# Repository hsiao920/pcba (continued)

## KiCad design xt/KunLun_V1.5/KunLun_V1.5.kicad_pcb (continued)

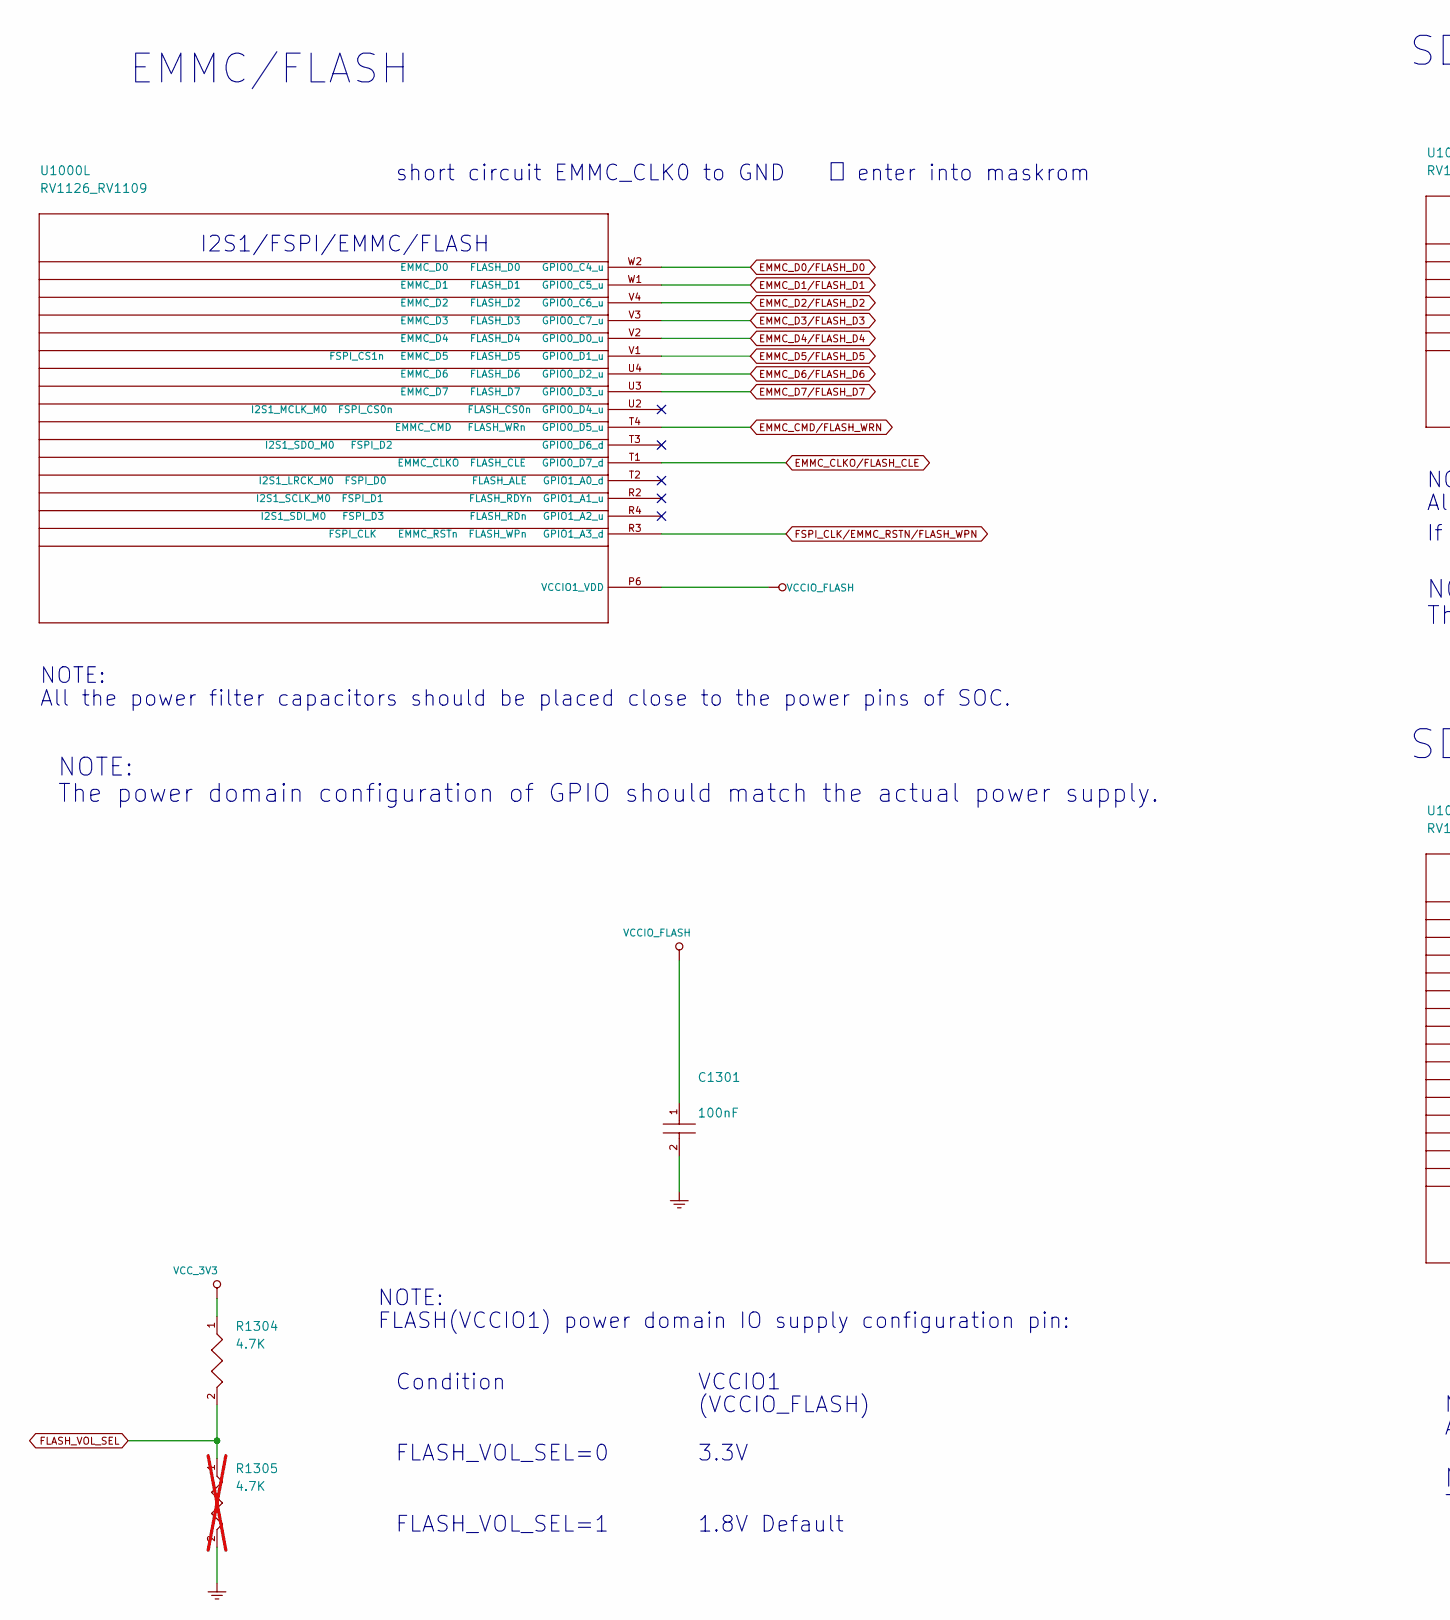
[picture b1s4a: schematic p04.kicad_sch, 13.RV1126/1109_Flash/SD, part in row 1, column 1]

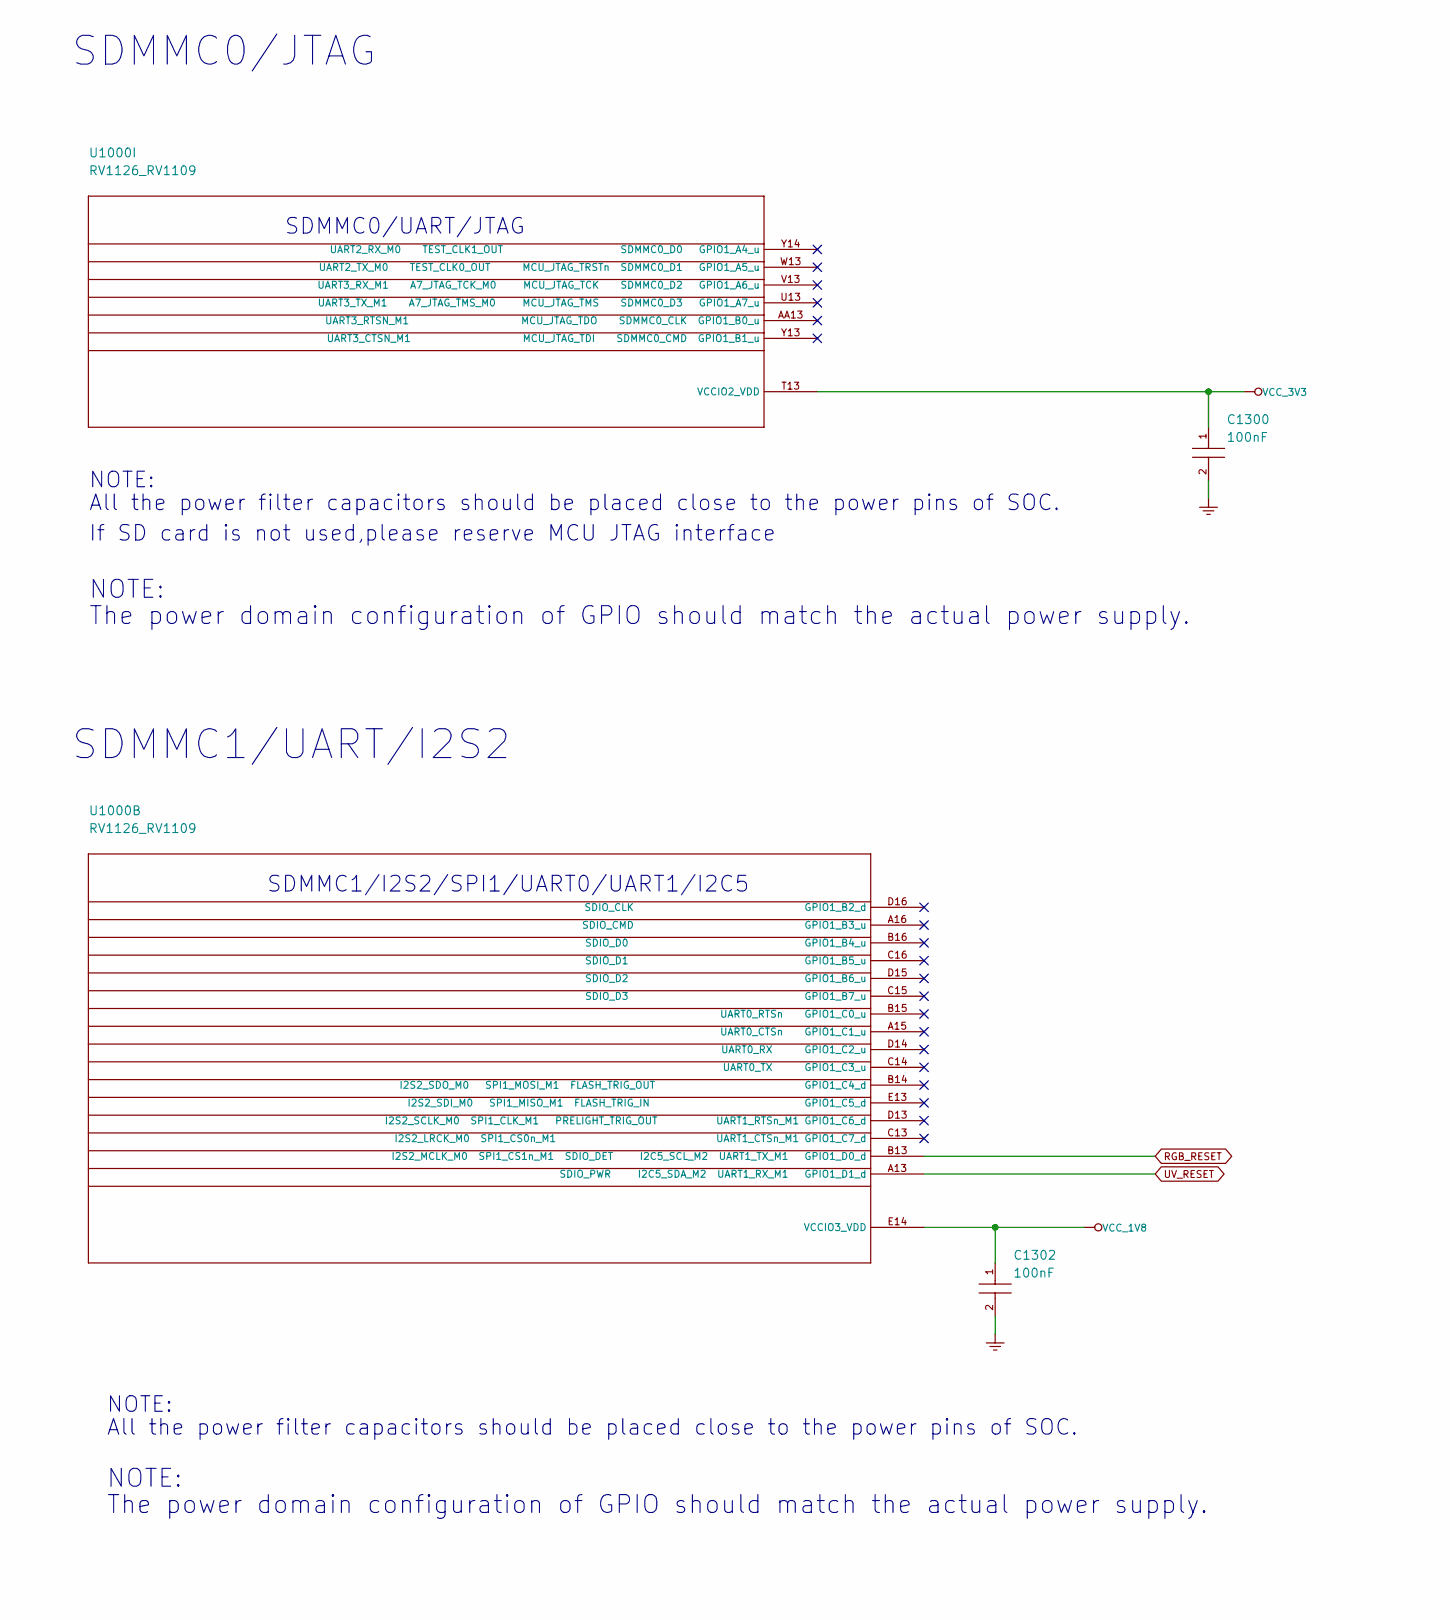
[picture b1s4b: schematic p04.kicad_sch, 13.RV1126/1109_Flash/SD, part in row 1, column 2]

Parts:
C1300, C1301, C1302: 100nF; C0201
R1304: 4.7K; R0402
R1305: 4.7K; R0402; not fitted
U1000: RV1126_RV1109; BGA409_14R00X14R00X0R90

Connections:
EMMC_CLKO/FLASH_CLE: U1000.T1 (EMMC_CLKO FLASH_CLE GPIO0_D7_d); also elsewhere on the board
EMMC_CMD/FLASH_WRN: U1000.T4 (EMMC_CMD FLASH_WRn GPIO0_D5_u); also elsewhere on the board
EMMC_D0/FLASH_D0: U1000.W2 (EMMC_D0 FLASH_D0 GPIO0_C4_u); also elsewhere on the board
EMMC_D1/FLASH_D1: U1000.W1 (EMMC_D1 FLASH_D1 GPIO0_C5_u); also elsewhere on the board
EMMC_D2/FLASH_D2: U1000.V4 (EMMC_D2 FLASH_D2 GPIO0_C6_u); also elsewhere on the board
EMMC_D3/FLASH_D3: U1000.V3 (EMMC_D3 FLASH_D3 GPIO0_C7_u); also elsewhere on the board
EMMC_D4/FLASH_D4: U1000.V2 (EMMC_D4 FLASH_D4 GPIO0_D0_u); also elsewhere on the board
EMMC_D5/FLASH_D5: U1000.V1 (FSPI_CS1n EMMC_D5 FLASH_D5 GPIO0_D1_u); also elsewhere on the board
EMMC_D6/FLASH_D6: U1000.U4 (EMMC_D6 FLASH_D6 GPIO0_D2_u); also elsewhere on the board
EMMC_D7/FLASH_D7: U1000.U3 (EMMC_D7 FLASH_D7 GPIO0_D3_u); also elsewhere on the board
FLASH_VOL_SEL: R1304.2, R1305.1; also elsewhere on the board
FSPI_CLK/EMMC_RSTN/FLASH_WPN: U1000.R3 (FSPI_CLK EMMC_RSTn FLASH_WPn GPIO1_A3_d); also elsewhere on the board
GND: C1300.2, C1301.2, C1302.2, R1305.2; also elsewhere on the board
RGB_RESET: U1000.B13 (I2S2_MCLK_M0 SPI1_CS1n_M1 SDIO_DET I2C5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); also elsewhere on the board
UV_RESET: U1000.A13 (SDIO_PWR I2C5_SDA_M2 UART1_RX_M1 GPIO1_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); also elsewhere on the board
VCCIO_FLASH: C1301.1, U1000.P6 (VCCIO1_VDD); also elsewhere on the board
VCC_1V8: C1302.1, U1000.E14 (VCCIO3_VDD); also elsewhere on the board
VCC_3V3: C1300.1, R1304.1, U1000.T13 (VCCIO2_VDD); also elsewhere on the board

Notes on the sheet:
EMMC/FLASH
SDMMC0/JTAG
SDMMC1/UART/I2S2
NOTE:
All the power filter capacitors should be placed close to the power pins of SOC.
FLASH(VCCIO1) power domain IO supply configuration pin:
3.3V
1.8V Default
FLASH_VOL_SEL=0
FLASH_VOL_SEL=1
VCCIO1
(VCCIO_FLASH)
Condition
If SD card is not used,please reserve MCU JTAG interface
The power domain configuration of GPIO should match the actual power supply.
short circuit EMMC_CLK0 to GND
enter into maskrom
SDMMC0/UART/JTAG
SDMMC1/I2S2/SPI1/UART0/UART1/I2C5
I2S1/FSPI/EMMC/FLASH

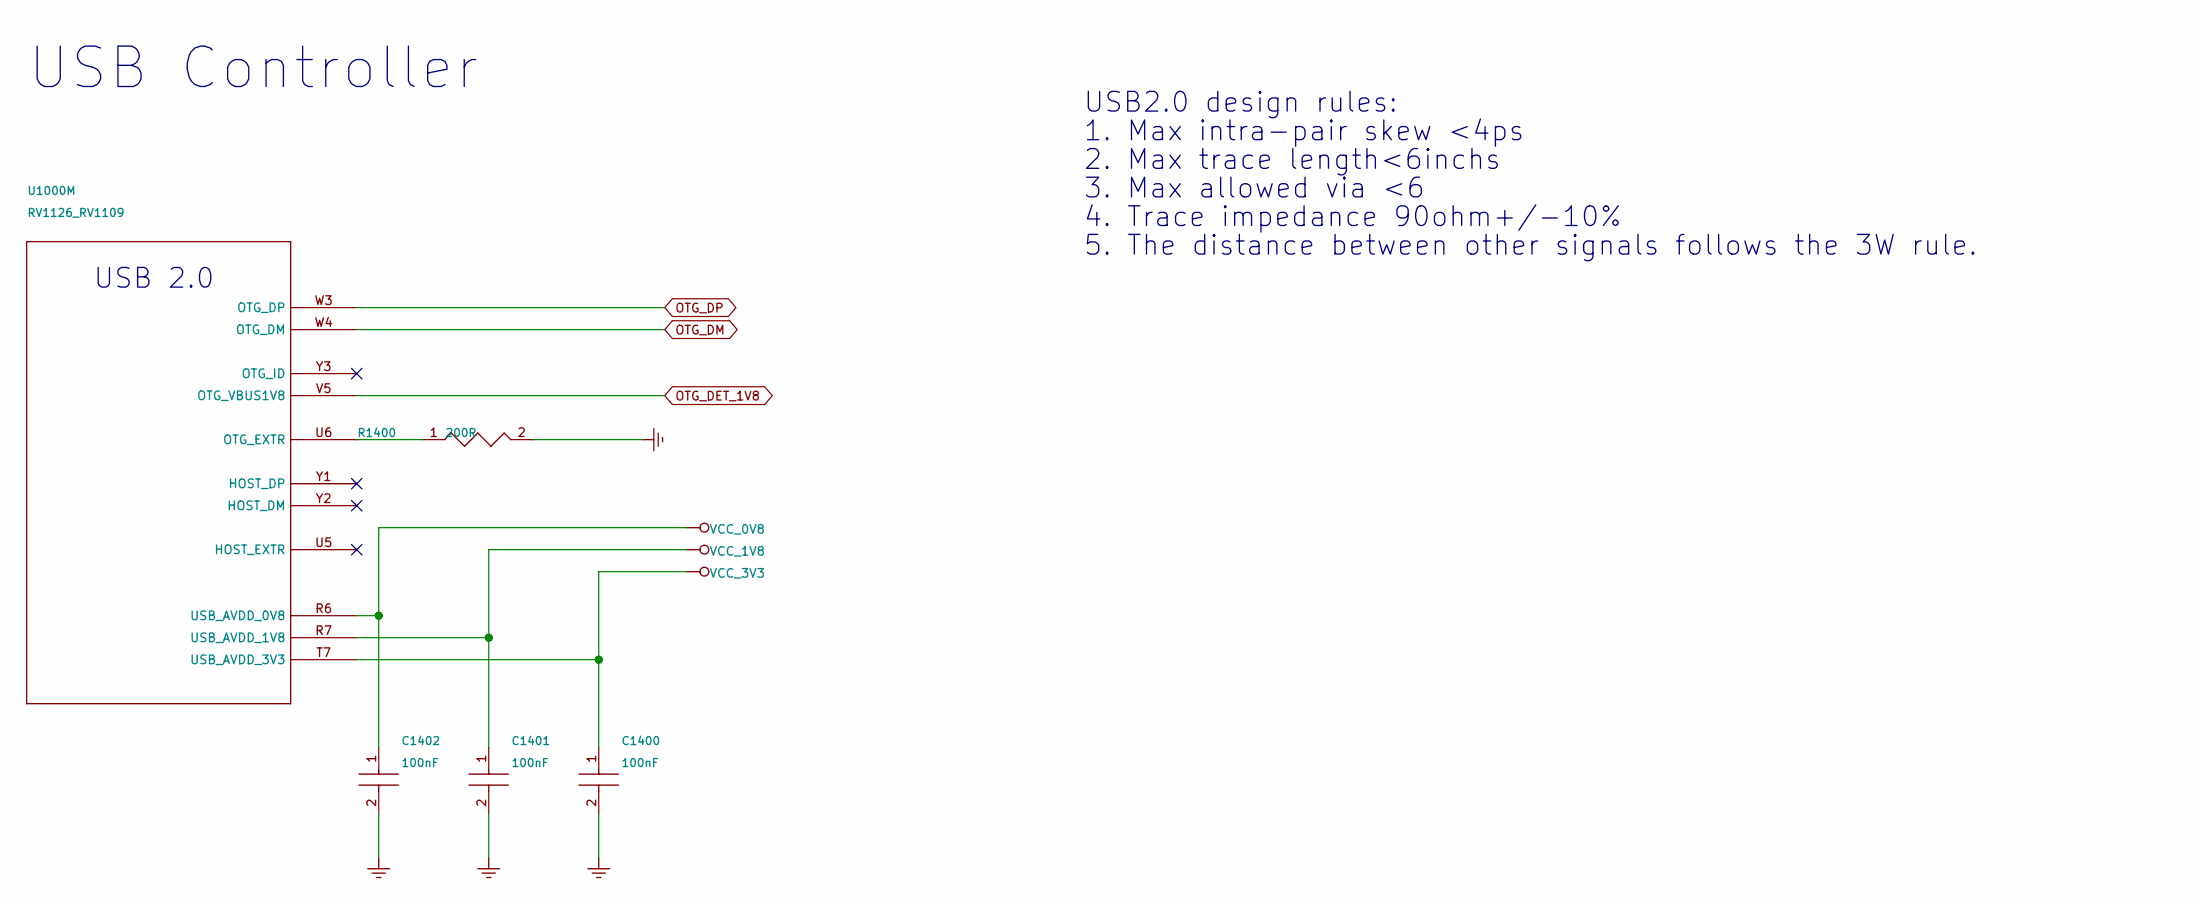
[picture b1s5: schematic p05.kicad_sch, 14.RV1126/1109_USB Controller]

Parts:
C1400, C1401, C1402: 100nF; C0201
R1400: 200R; R0402
U1000: RV1126_RV1109; BGA409_14R00X14R00X0R90

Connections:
GND: C1400.2, C1401.2, C1402.2, R1400.2; also elsewhere on the board
unnamed: R1400.1, U1000.U6 (OTG_EXTR)
OTG_DET_1V8: U1000.V5 (OTG_VBUS1V8); also elsewhere on the board
OTG_DM: U1000.W4 (OTG_DM); also elsewhere on the board
OTG_DP: U1000.W3 (OTG_DP); also elsewhere on the board
VCC_0V8: C1402.1, U1000.R6 (USB_AVDD_0V8); also elsewhere on the board
VCC_1V8: C1401.1, U1000.R7 (USB_AVDD_1V8); also elsewhere on the board
VCC_3V3: C1400.1, U1000.T7 (USB_AVDD_3V3); also elsewhere on the board

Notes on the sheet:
USB Controller
USB2.0 design rules:
1. Max intra-pair skew <4ps
2. Max trace length<6inchs
3. Max allowed via <6
4. Trace impedance 90ohm+/-10%
5. The distance between other signals follows the 3W rule.
USB 2.0

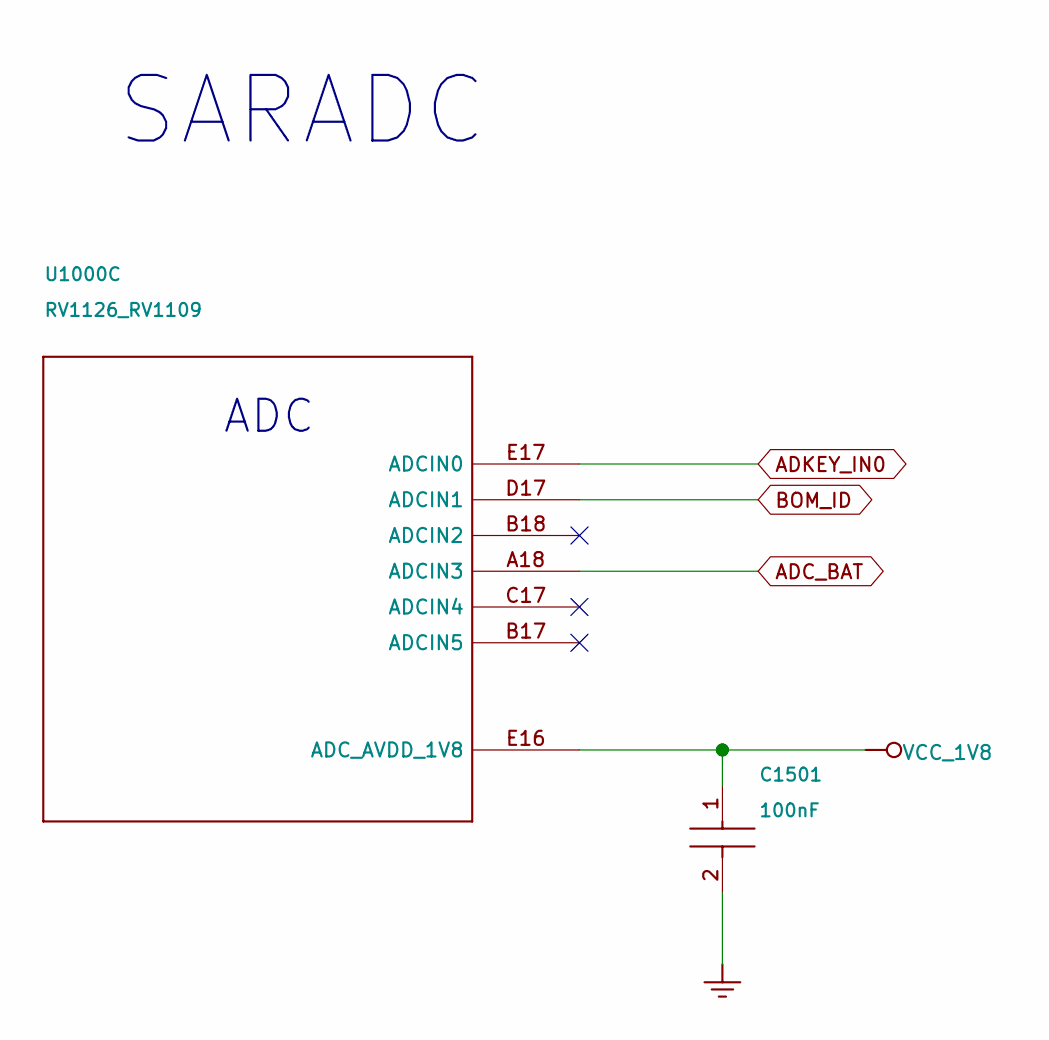
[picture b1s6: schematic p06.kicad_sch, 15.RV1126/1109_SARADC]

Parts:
C1501: 100nF; C0201
U1000: RV1126_RV1109; BGA409_14R00X14R00X0R90

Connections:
ADC_BAT: U1000.A18 (ADCIN3); also elsewhere on the board
ADKEY_IN0: U1000.E17 (ADCIN0)
BOM_ID: U1000.D17 (ADCIN1)
GND: C1501.2; also elsewhere on the board
VCC_1V8: C1501.1, U1000.E16 (ADC_AVDD_1V8); also elsewhere on the board

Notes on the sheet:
SARADC
ADC

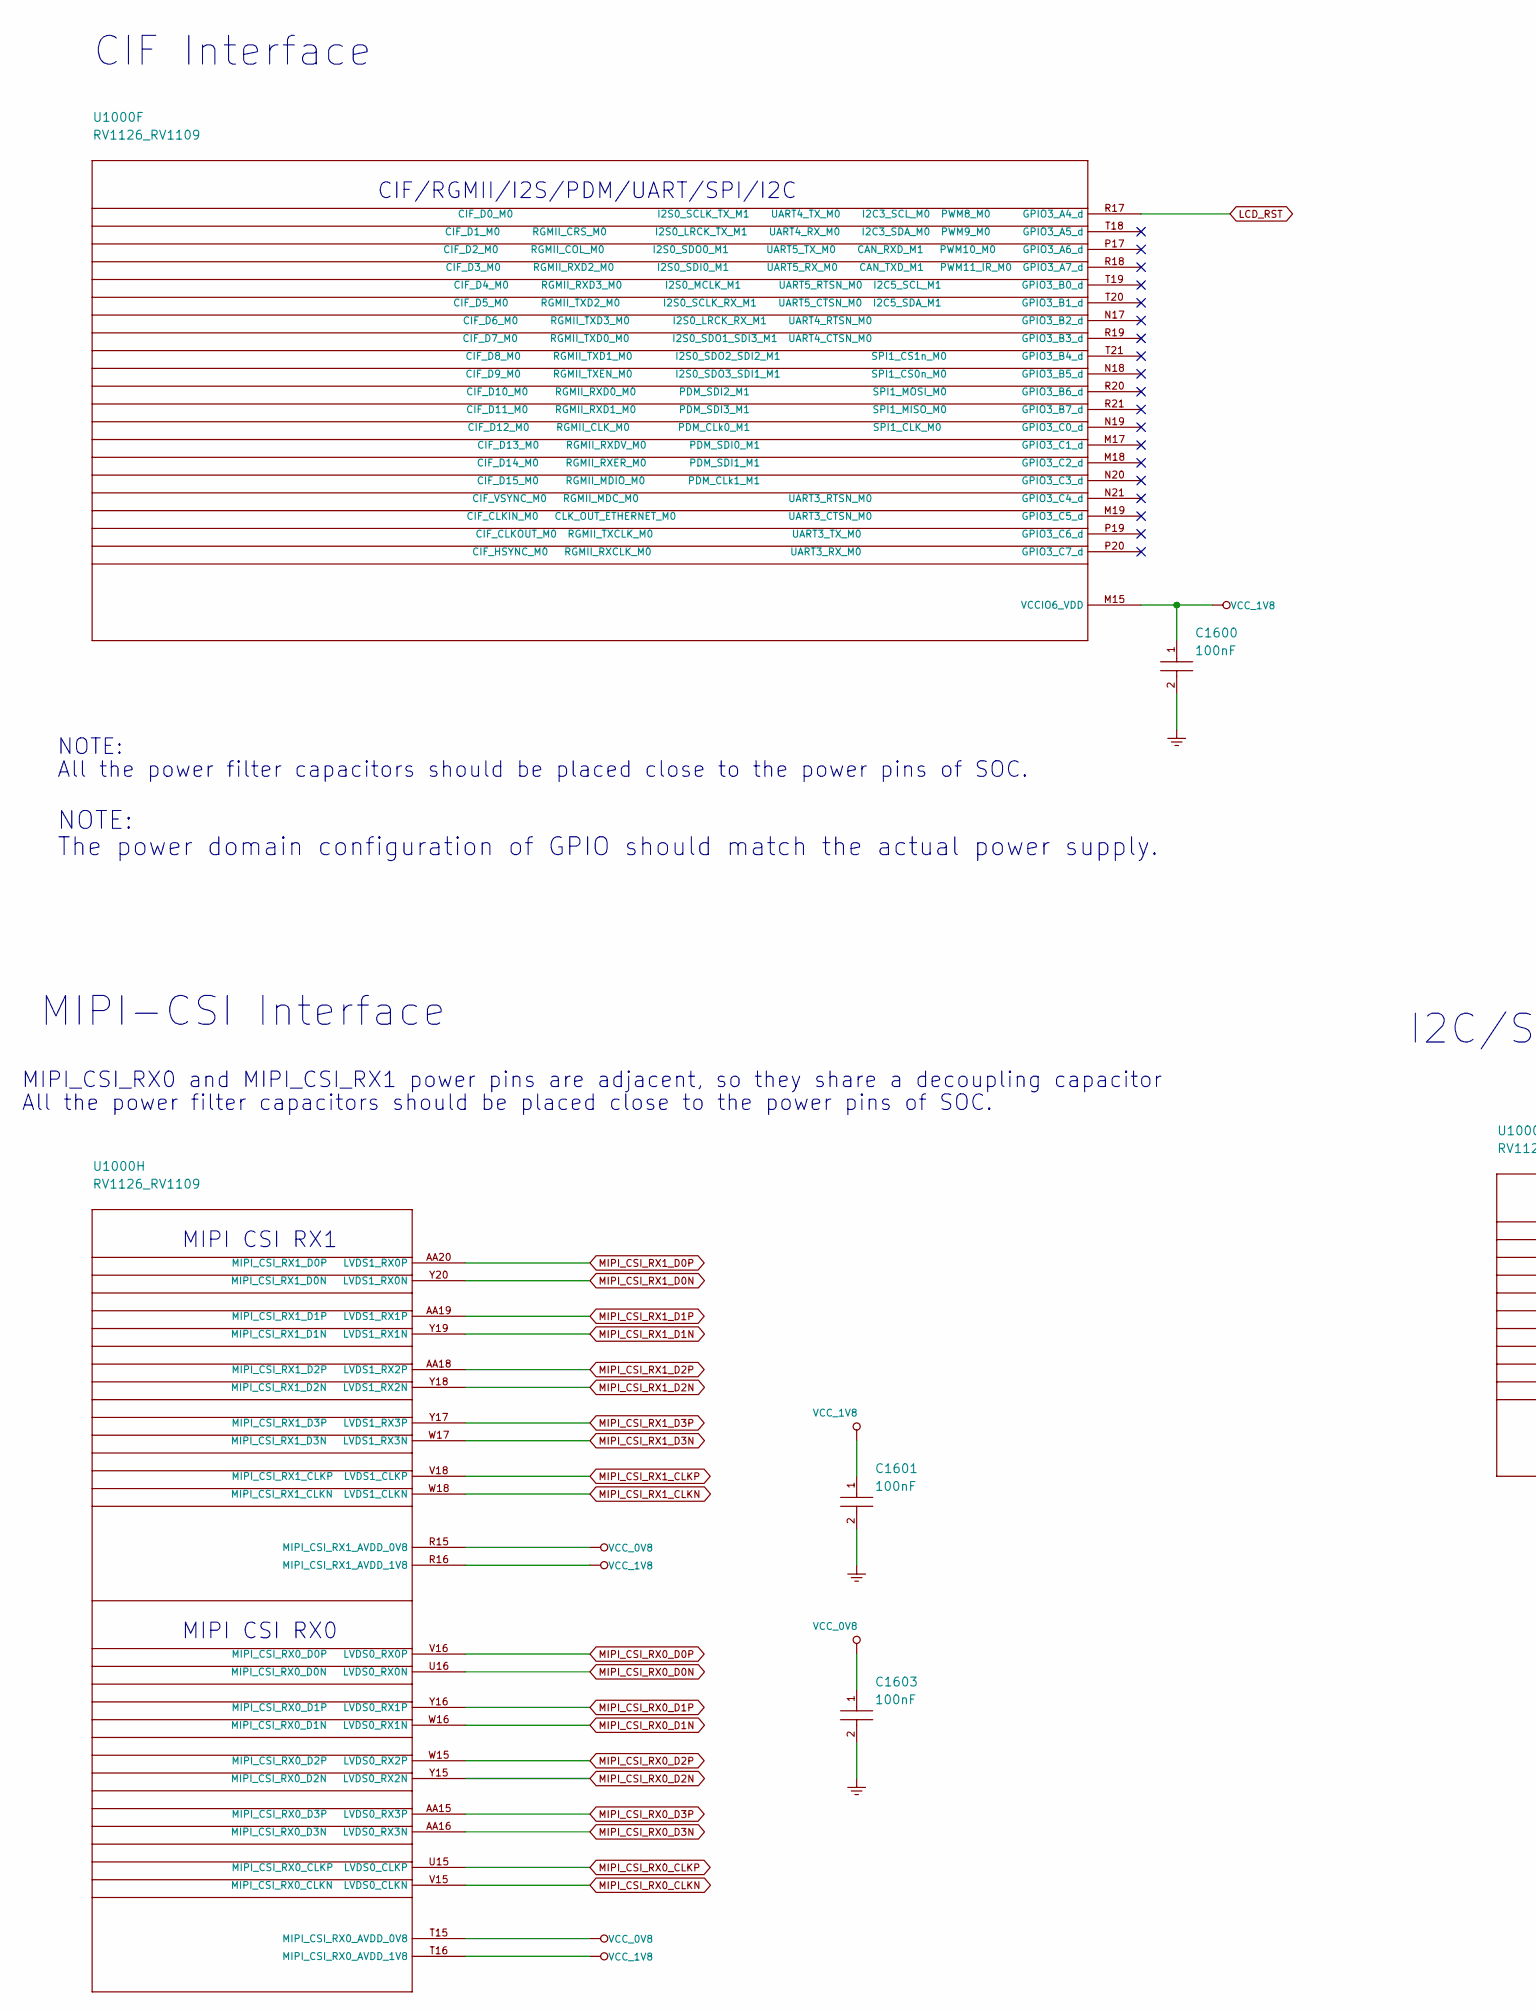
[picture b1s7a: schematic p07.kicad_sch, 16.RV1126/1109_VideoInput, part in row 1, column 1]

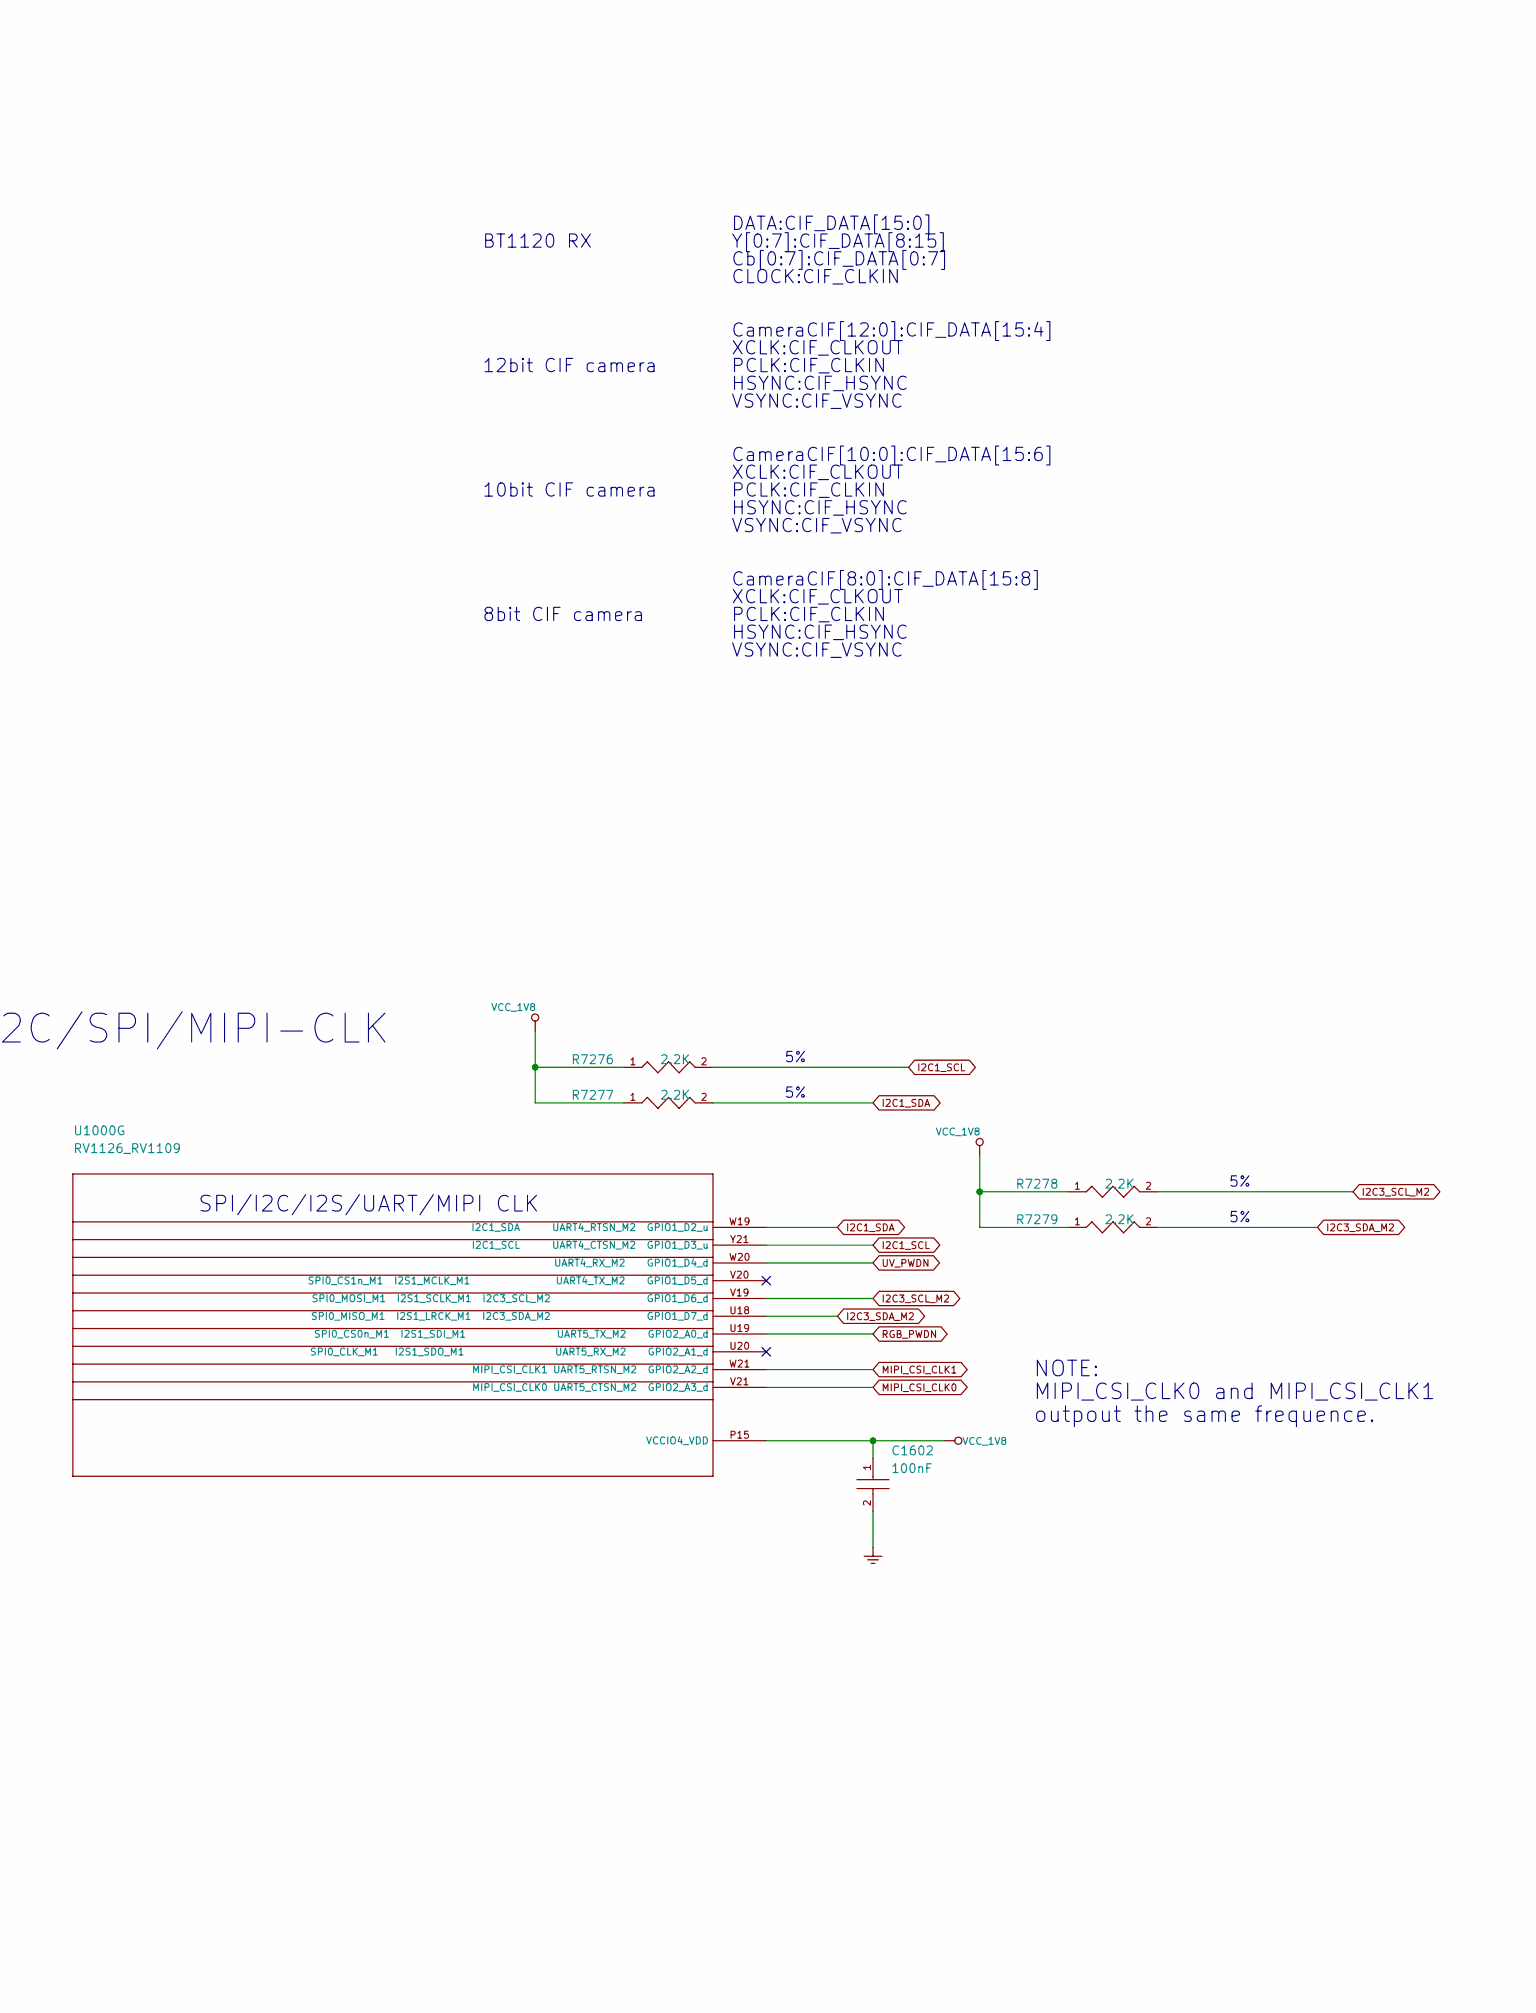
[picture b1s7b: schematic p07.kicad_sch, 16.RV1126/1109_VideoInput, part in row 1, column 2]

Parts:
C1600, C1601, C1602, C1603: 100nF; C0201
R7276, R7277, R7278, R7279: 2.2K; R0402
U1000: RV1126_RV1109; BGA409_14R00X14R00X0R90

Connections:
GND: C1600.2, C1601.2, C1602.2, C1603.2; also elsewhere on the board
I2C1_SCL: R7276.2, U1000.Y21 (I2C1_SCL UART4_CTSN_M2 GPIO1_D3_u); also elsewhere on the board
I2C1_SDA: R7277.2, U1000.W19 (I2C1_SDA UART4_RTSN_M2 GPIO1_D2_u); also elsewhere on the board
I2C3_SCL_M2: R7278.2, U1000.V19 (SPI0_MOSI_M1 I2S1_SCLK_M1 I2C3_SCL_M2 G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); also elsewhere on the board
I2C3_SDA_M2: R7279.2, U1000.U18 (SPI0_MISO_M1 I2S1_LRCK_M1 I2C3_SDA_M2 G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); also elsewhere on the board
LCD_RST: U1000.R17 (CIF_D0_M0 I2S0_SCLK_TX_M1 UART4_TX_M0 I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); also elsewhere on the board
MIPI_CSI_CLK0: U1000.V21 (MIPI_CSI_CLK0 UART5_CTSN_M2 GPIO2_A3_d); also elsewhere on the board
MIPI_CSI_CLK1: U1000.W21 (MIPI_CSI_CLK1 UART5_RTSN_M2 GPIO2_A2_d); also elsewhere on the board
MIPI_CSI_RX0_CLKN: U1000.V15 (MIPI_CSI_RX0_CLKN LVDS0_CLKN); also elsewhere on the board
MIPI_CSI_RX0_CLKP: U1000.U15 (MIPI_CSI_RX0_CLKP LVDS0_CLKP); also elsewhere on the board
MIPI_CSI_RX0_D0N: U1000.U16 (MIPI_CSI_RX0_D0N LVDS0_RX0N); also elsewhere on the board
MIPI_CSI_RX0_D0P: U1000.V16 (MIPI_CSI_RX0_D0P LVDS0_RX0P); also elsewhere on the board
MIPI_CSI_RX0_D1N: U1000.W16 (MIPI_CSI_RX0_D1N LVDS0_RX1N); also elsewhere on the board
MIPI_CSI_RX0_D1P: U1000.Y16 (MIPI_CSI_RX0_D1P LVDS0_RX1P); also elsewhere on the board
MIPI_CSI_RX0_D2N: U1000.Y15 (MIPI_CSI_RX0_D2N LVDS0_RX2N)
MIPI_CSI_RX0_D2P: U1000.W15 (MIPI_CSI_RX0_D2P LVDS0_RX2P)
MIPI_CSI_RX0_D3N: U1000.AA16 (MIPI_CSI_RX0_D3N LVDS0_RX3N)
MIPI_CSI_RX0_D3P: U1000.AA15 (MIPI_CSI_RX0_D3P LVDS0_RX3P)
MIPI_CSI_RX1_CLKN: U1000.W18 (MIPI_CSI_RX1_CLKN LVDS1_CLKN); also elsewhere on the board
MIPI_CSI_RX1_CLKP: U1000.V18 (MIPI_CSI_RX1_CLKP LVDS1_CLKP); also elsewhere on the board
MIPI_CSI_RX1_D0N: U1000.Y20 (MIPI_CSI_RX1_D0N LVDS1_RX0N); also elsewhere on the board
MIPI_CSI_RX1_D0P: U1000.AA20 (MIPI_CSI_RX1_D0P LVDS1_RX0P); also elsewhere on the board
MIPI_CSI_RX1_D1N: U1000.Y19 (MIPI_CSI_RX1_D1N LVDS1_RX1N); also elsewhere on the board
MIPI_CSI_RX1_D1P: U1000.AA19 (MIPI_CSI_RX1_D1P LVDS1_RX1P); also elsewhere on the board
MIPI_CSI_RX1_D2N: U1000.Y18 (MIPI_CSI_RX1_D2N LVDS1_RX2N)
MIPI_CSI_RX1_D2P: U1000.AA18 (MIPI_CSI_RX1_D2P LVDS1_RX2P)
MIPI_CSI_RX1_D3N: U1000.W17 (MIPI_CSI_RX1_D3N LVDS1_RX3N)
MIPI_CSI_RX1_D3P: U1000.Y17 (MIPI_CSI_RX1_D3P LVDS1_RX3P)
RGB_PWDN: U1000.U19 (SPI0_CS0n_M1 I2S1_SDI_M1 UART5_TX_M2 GP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); also elsewhere on the board
UV_PWDN: U1000.W20 (UART4_RX_M2 GPIO1_D4_d); also elsewhere on the board
VCC_0V8: C1603.1, U1000.R15 (MIPI_CSI_RX1_AVDD_0V8), U1000.T15 (MIPI_CSI_RX0_AVDD_0V8); also elsewhere on the board
VCC_1V8: C1600.1, C1601.1, C1602.1, R7276.1, R7277.1, R7278.1, R7279.1, U1000.M15 (VCCIO6_VDD), U1000.P15 (VCCIO4_VDD), U1000.R16 (MIPI_CSI_RX1_AVDD_1V8), U1000.T16 (MIPI_CSI_RX0_AVDD_1V8); also elsewhere on the board

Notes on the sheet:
CIF Interface
MIPI-CSI Interface
I2C/SPI/MIPI-CLK
MIPI_CSI_RX0 and MIPI_CSI_RX1 power pins are adjacent, so they share a decoupling capacitor
All the power filter capacitors should be placed close to the power pins of SOC.
BT1120 RX
DATA:CIF_DATA[15:0]
Y[0:7]:CIF_DATA[8:15]
Cb[0:7]:CIF_DATA[0:7]
CLOCK:CIF_CLKIN
12bit CIF camera
CameraCIF[12:0]:CIF_DATA[15:4]
XCLK:CIF_CLKOUT
HSYNC:CIF_HSYNC
VSYNC:CIF_VSYNC
PCLK:CIF_CLKIN
10bit CIF camera
CameraCIF[10:0]:CIF_DATA[15:6]
8bit CIF camera
CameraCIF[8:0]:CIF_DATA[15:8]
NOTE:
MIPI_CSI_CLK0 and MIPI_CSI_CLK1
outpout the same frequence.
The power domain configuration of GPIO should match the actual power supply.
MIPI CSI RX1
MIPI CSI RX0
SPI/I2C/I2S/UART/MIPI CLK
CIF/RGMII/I2S/PDM/UART/SPI/I2C
